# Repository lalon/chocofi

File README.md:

# chocofi

Keyboard shield and 3d printed case to use with Arduino ProMicro-like contoller.

- Split keyboard with 3 rows, 5 columns, and 3 thumbs per half
- Increased pinky column stagger
- Inspired by [Fifi keyboard](https://github.com/raychengy/fifi_split_keeb)
- Double-sided pcb (pcb can be used as left or right half)
- Pro Micro compatible footprint
- Easy to print, FDM-friendly two-piece case

## Artifacts

Gerbers are here: [pcb](/pcb/gerber.zip) and [top plate](/pcb/gerber-plate.zip)

Stls are here: [case folder](/case)

For more photos check out the [images folder](/images)

## By the way

Awesome libs used:

- [kbd.pretty](https://github.com/foostan/kbd) by foostan
- [keyswitches.pretty](https://github.com/daprice/keyswitches.pretty) by daprice

Also closest alternatives are:

- [raychengy/fifi](https://github.com/raychengy/fifi_split_keeb): non choc (mx switches)
- [davidphilipbarr/chocorne](https://github.com/davidphilipbarr/36keys/tree/master/42Keys/chocorne): non hotswap but choc-spaced corne (you can break off one column so it will be 5x3, but with corne pinky stagger)

This Fork enlarges one of the mounting holes (H7) and centers it to accommodate a trackpoint.
Hasn't been tested yet.

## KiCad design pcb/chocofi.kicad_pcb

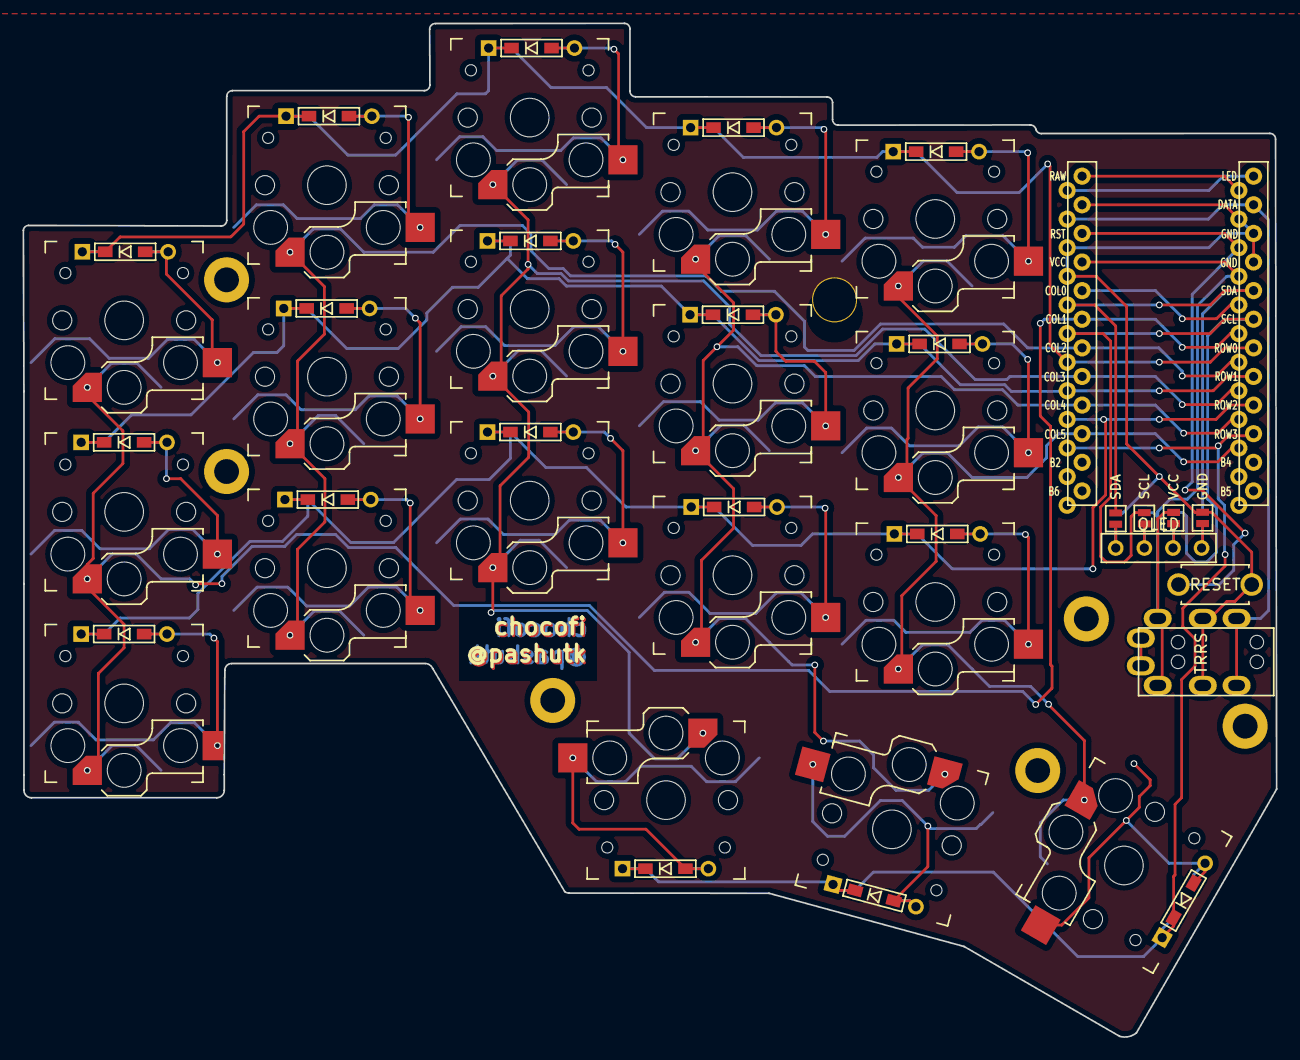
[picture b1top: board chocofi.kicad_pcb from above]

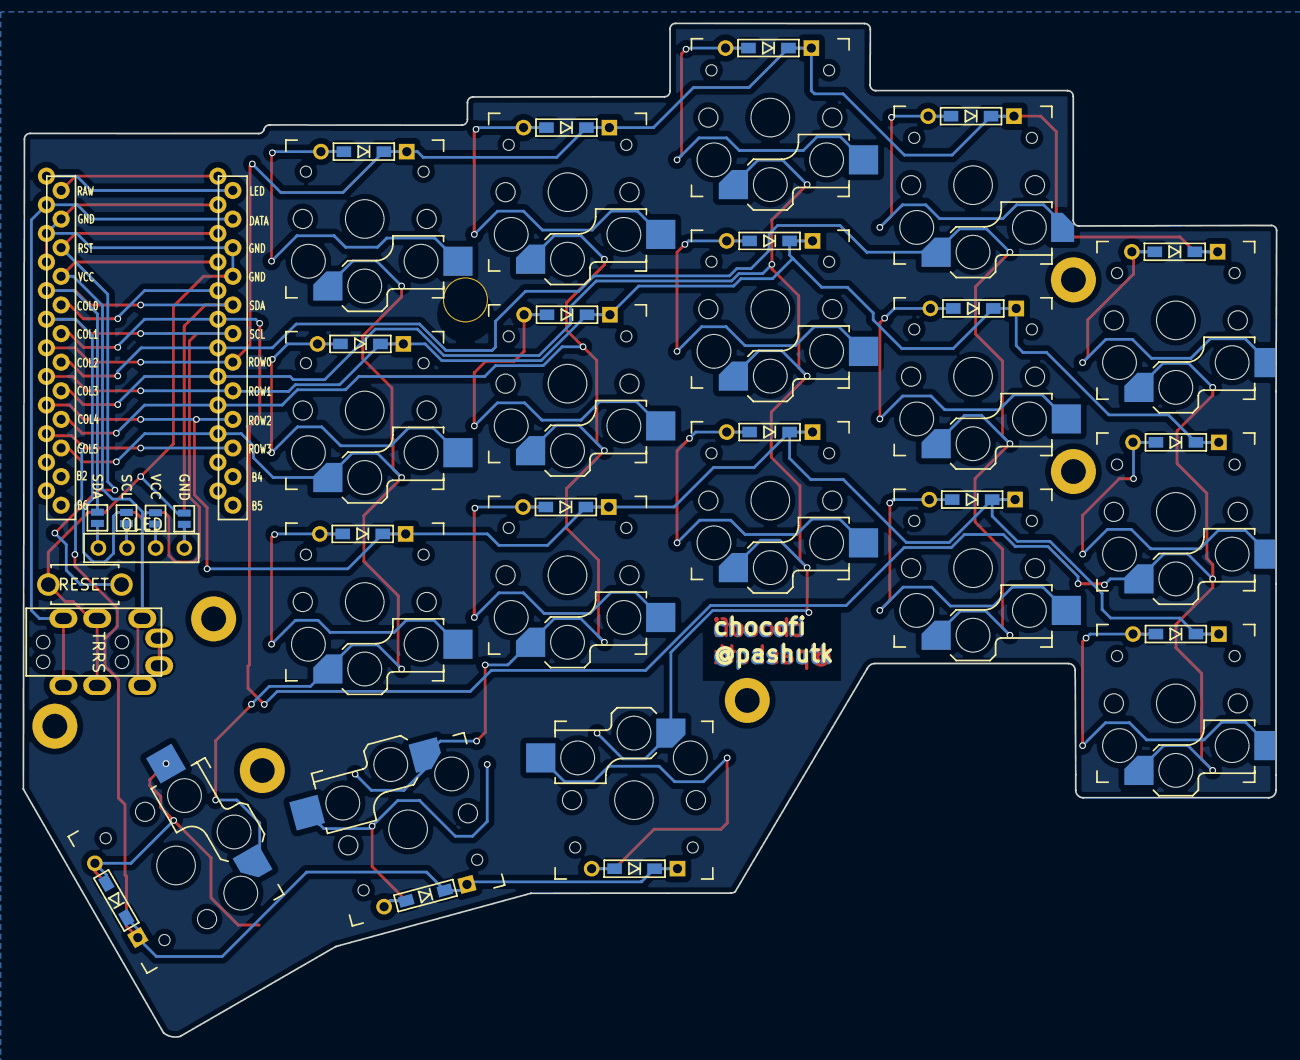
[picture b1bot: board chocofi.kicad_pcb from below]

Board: 2 copper layers, 111.3 x 90.0 mm, 55 parts (4 on the bottom side), 37 nets.

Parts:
D2, D3, D4, D5, D6, D8, D9, D10, D11, D12, D14, D15, D16, D17, D18, D19, D20, D21: D; D3_TH_SMD
H1: h1; LEGO_HOLE
J1: MJ-4PP-9
J2: OLED
JP6, JP61: SDA; Jumper
JP62, JP68: GND; Jumper
JP63, JP66: SCL; Jumper
JP64, JP65: VCC; Jumper
RSW1: Val**; ResetSW
SW2, SW3, SW4, SW5, SW6, SW8, SW9, SW10, SW11, SW12, SW14, SW15, SW16, SW17, SW18, SW19, SW20, SW21: SW_PUSH; Kailh_socket_PG1350_reversible
U1: ProMicro; ProMicro_v2
h2: h2; LEGO_HOLE
h3: h3; LEGO_HOLE
h4: h4; LEGO_HOLE
h5: h5; LEGO_HOLE
h6: h6; LEGO_HOLE
h7: h7; LEGO_HOLE

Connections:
GND: J1.C, JP62.1, JP68.1, RSW1.1, U1.3, U1.4, U1.23
unnamed: D2.2, SW2.2
unnamed: D3.2, SW3.2
unnamed: D4.2, SW4.2
unnamed: D5.2, SW5.2
unnamed: D6.2, SW6.2
unnamed: D8.2, SW8.2
unnamed: D9.2, SW9.2
unnamed: D10.2, SW10.2
unnamed: D11.2, SW11.2
unnamed: D12.2, SW12.2
unnamed: D14.2, SW14.2
unnamed: D15.2, SW15.2
unnamed: D16.2, SW16.2
unnamed: D17.2, SW17.2
unnamed: D18.2, SW18.2
unnamed: D19.2, SW19.2
unnamed: D20.2, SW20.2
unnamed: D21.2, SW21.2
unnamed: J2.3, JP65.2, JP66.2
unnamed: J2.4, JP6.2, JP68.2
unnamed: J2.2, JP63.2, JP64.2
unnamed: J2.1, JP61.2, JP62.2
SCL: JP63.1, JP66.1, U1.6
SDA: JP6.1, JP61.1, U1.5
VCC: J1.D, JP64.1, JP65.1, U1.21
col1: SW2.1, SW8.1, SW14.1, U1.19
col2: SW3.1, SW9.1, SW15.1, U1.18
col3: SW4.1, SW10.1, SW16.1, SW19.1, U1.17
col4: SW5.1, SW11.1, SW17.1, SW20.1, U1.16
col5: SW6.1, SW12.1, SW18.1, SW21.1, U1.15
data: J1.B, U1.2
reset: RSW1.2, U1.22
row0: D2.1, D3.1, D4.1, D5.1, D6.1, U1.7
row1: D8.1, D9.1, D10.1, D11.1, D12.1, U1.8
row2: D14.1, D15.1, D16.1, D17.1, D18.1, U1.9
row3: D19.1, D20.1, D21.1, U1.10

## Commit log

2022-03-27 Enlarged hole for trackpoint
2022-03-27 Readme - Trackpoint hole
